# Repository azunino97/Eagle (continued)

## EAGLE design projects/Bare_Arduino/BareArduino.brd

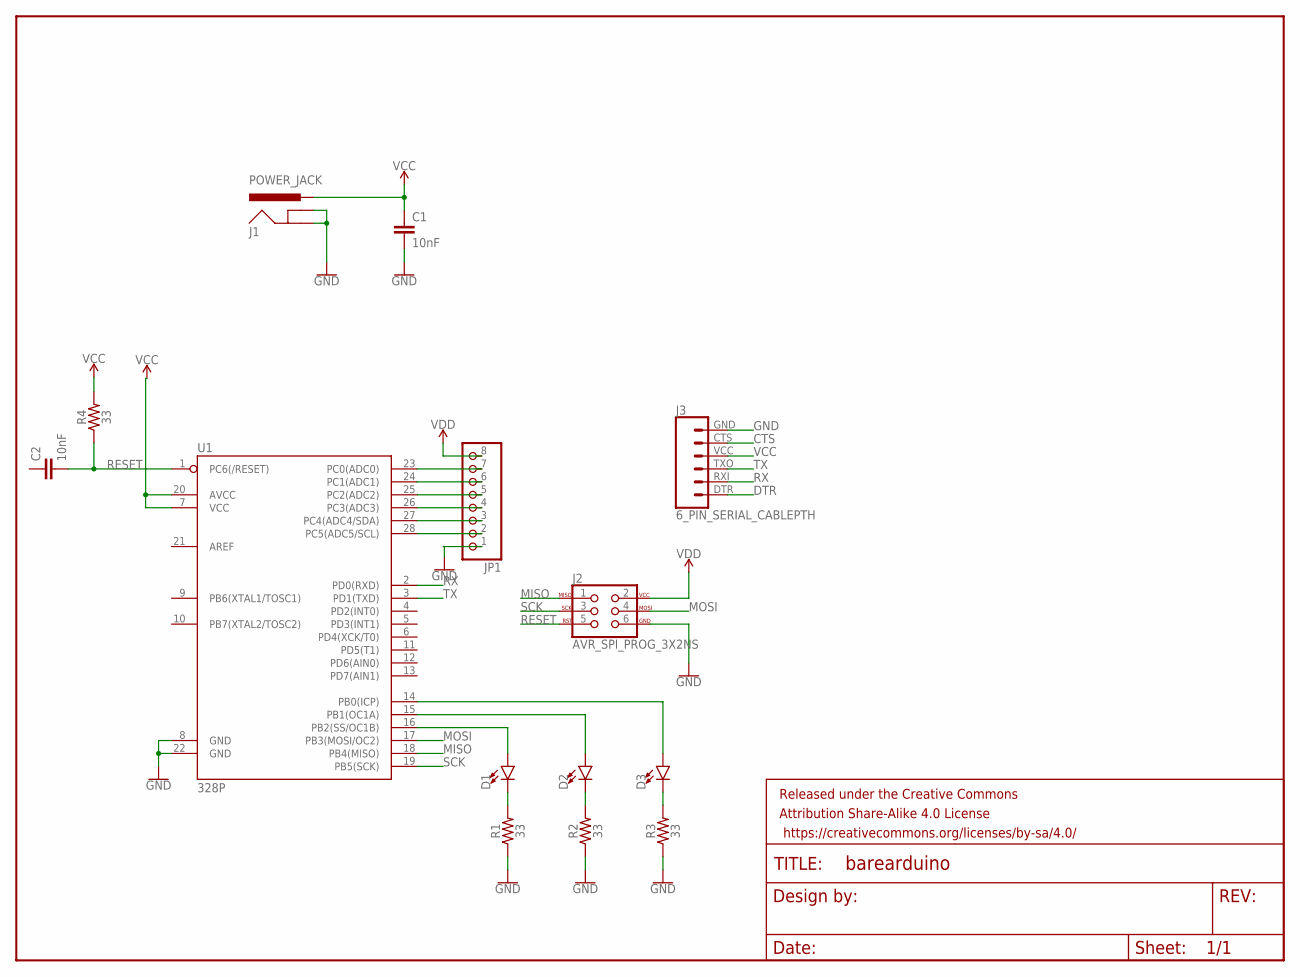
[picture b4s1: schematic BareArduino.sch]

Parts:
C1: 10nF; CAP-PTH-10MM
C2: 10nF; 0603
D1, D2, D3: LED5MM; LED_5MM
FRAME1: FRAME-LETTER; CREATIVE_COMMONS
J1: POWER_JACK; POWER_JACK_PTH
J2: AVR_SPI_PROG_3X2NS; 2X3-NS
J3: 6_PIN_SERIAL_CABLEPTH; FTDI_BASIC
JP1: PINHD-1X8; 1X08
R1, R2, R3, R4: 33; 0603
U1: 328P; DIP28

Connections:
CTS: J3.CTS (5)
DTR: J3.DTR (1)
GND: C1.2, J1.GND, J1.GNDBREAK, J2.6, J3.GND (6), JP1.1, R1.1, R2.1, R3.1, U1.8 (GND), U1.22 (GND)
MISO: J2.1, U1.18 (PB4(MISO))
MOSI: J2.4, U1.17 (PB3(MOSI/OC2))
unnamed: JP1.7, U1.23 (PC0(ADC0))
unnamed: JP1.6, U1.24 (PC1(ADC1))
unnamed: JP1.5, U1.25 (PC2(ADC2))
unnamed: JP1.4, U1.26 (PC3(ADC3))
unnamed: JP1.3, U1.27 (PC4(ADC4/SDA))
unnamed: JP1.2, U1.28 (PC5(ADC5/SCL))
unnamed: D1.K (C), R1.2
unnamed: D2.K (C), R2.2
unnamed: D3.K (C), R3.2
unnamed: D1.A, U1.16 (PB2(SS/OC1B))
unnamed: D2.A, U1.15 (PB1(OC1A))
unnamed: D3.A, U1.14 (PB0(ICP))
RESET: C2.2, J2.5, R4.1, U1.1 (PC6(/RESET))
RX: J3.RXI (2), U1.2 (PD0(RXD))
SCK: J2.3, U1.19 (PB5(SCK))
TX: J3.TXO (3), U1.3 (PD1(TXD))
VCC: C1.1, J1.PWR, J3.VCC (4), R4.2, U1.7 (VCC), U1.20 (AVCC)
VDD: J2.2, JP1.8

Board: 2 copper layers, 15 parts (0 on the bottom side), 21 nets, no tracks yet.

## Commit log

2020-06-17 adding all personal eagle files to Eagle/Personal
